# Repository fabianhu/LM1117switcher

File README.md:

# LM1117switcher
SOT-223 step down voltage regulator to replace LM1117-3.3 with a higher efficiency solution without redesigning the base board.
It fits directly onto the SOT223 Footprint of the LM1117.

Order the board at https://oshpark.com/shared_projects/o3DHlL3n

...here shown on top of a [ESPRGBLED board](https://github.com/fabianhu/ESPRGBLED)

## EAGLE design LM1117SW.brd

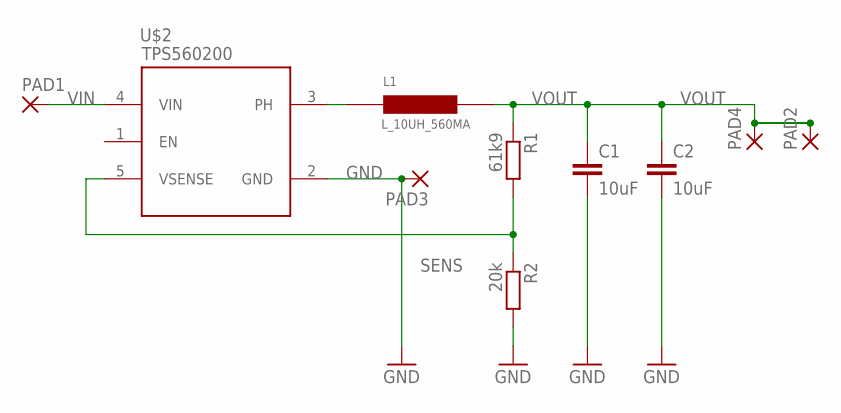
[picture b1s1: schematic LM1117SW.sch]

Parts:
C1, C2: 10uF; C0805K; MPN MC0805X106K250CT
L1: L_10UH_560MA; TYS3010100M-10; MPN TYS3010100M-10
PAD1, PAD2, PAD3, PAD4: 1,6/0,9
R1: 61k9; R0402; MPN MC00625W0402161K9
R2: 20k; R0402; MPN CRCW040220K0FKED
U$2: TPS560200; SOT23-5; MPN TPS560200DBVT

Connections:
GND: C1.2, C2.2, PAD3.1, R2.2, U$2.2 (GND)
unnamed: L1.P$1, U$2.3 (PH)
SENS: R1.2, R2.1, U$2.5 (VSENSE)
VIN: PAD1.1, U$2.4 (VIN)
VOUT: C1.1, C2.1, L1.P$2, PAD2.1, PAD4.1, R1.1

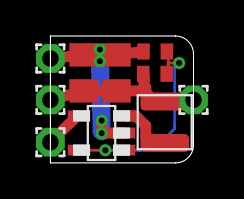
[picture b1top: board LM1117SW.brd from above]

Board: 2 copper layers, 8.0 x 7.0 mm, 10 parts (0 on the bottom side), 5 nets.

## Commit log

2015-08-17 ordered HW
2015-09-27 minor layout optimisation
    better soldering of inductor
2015-09-27 added images
2015-10-11 updated pad names
